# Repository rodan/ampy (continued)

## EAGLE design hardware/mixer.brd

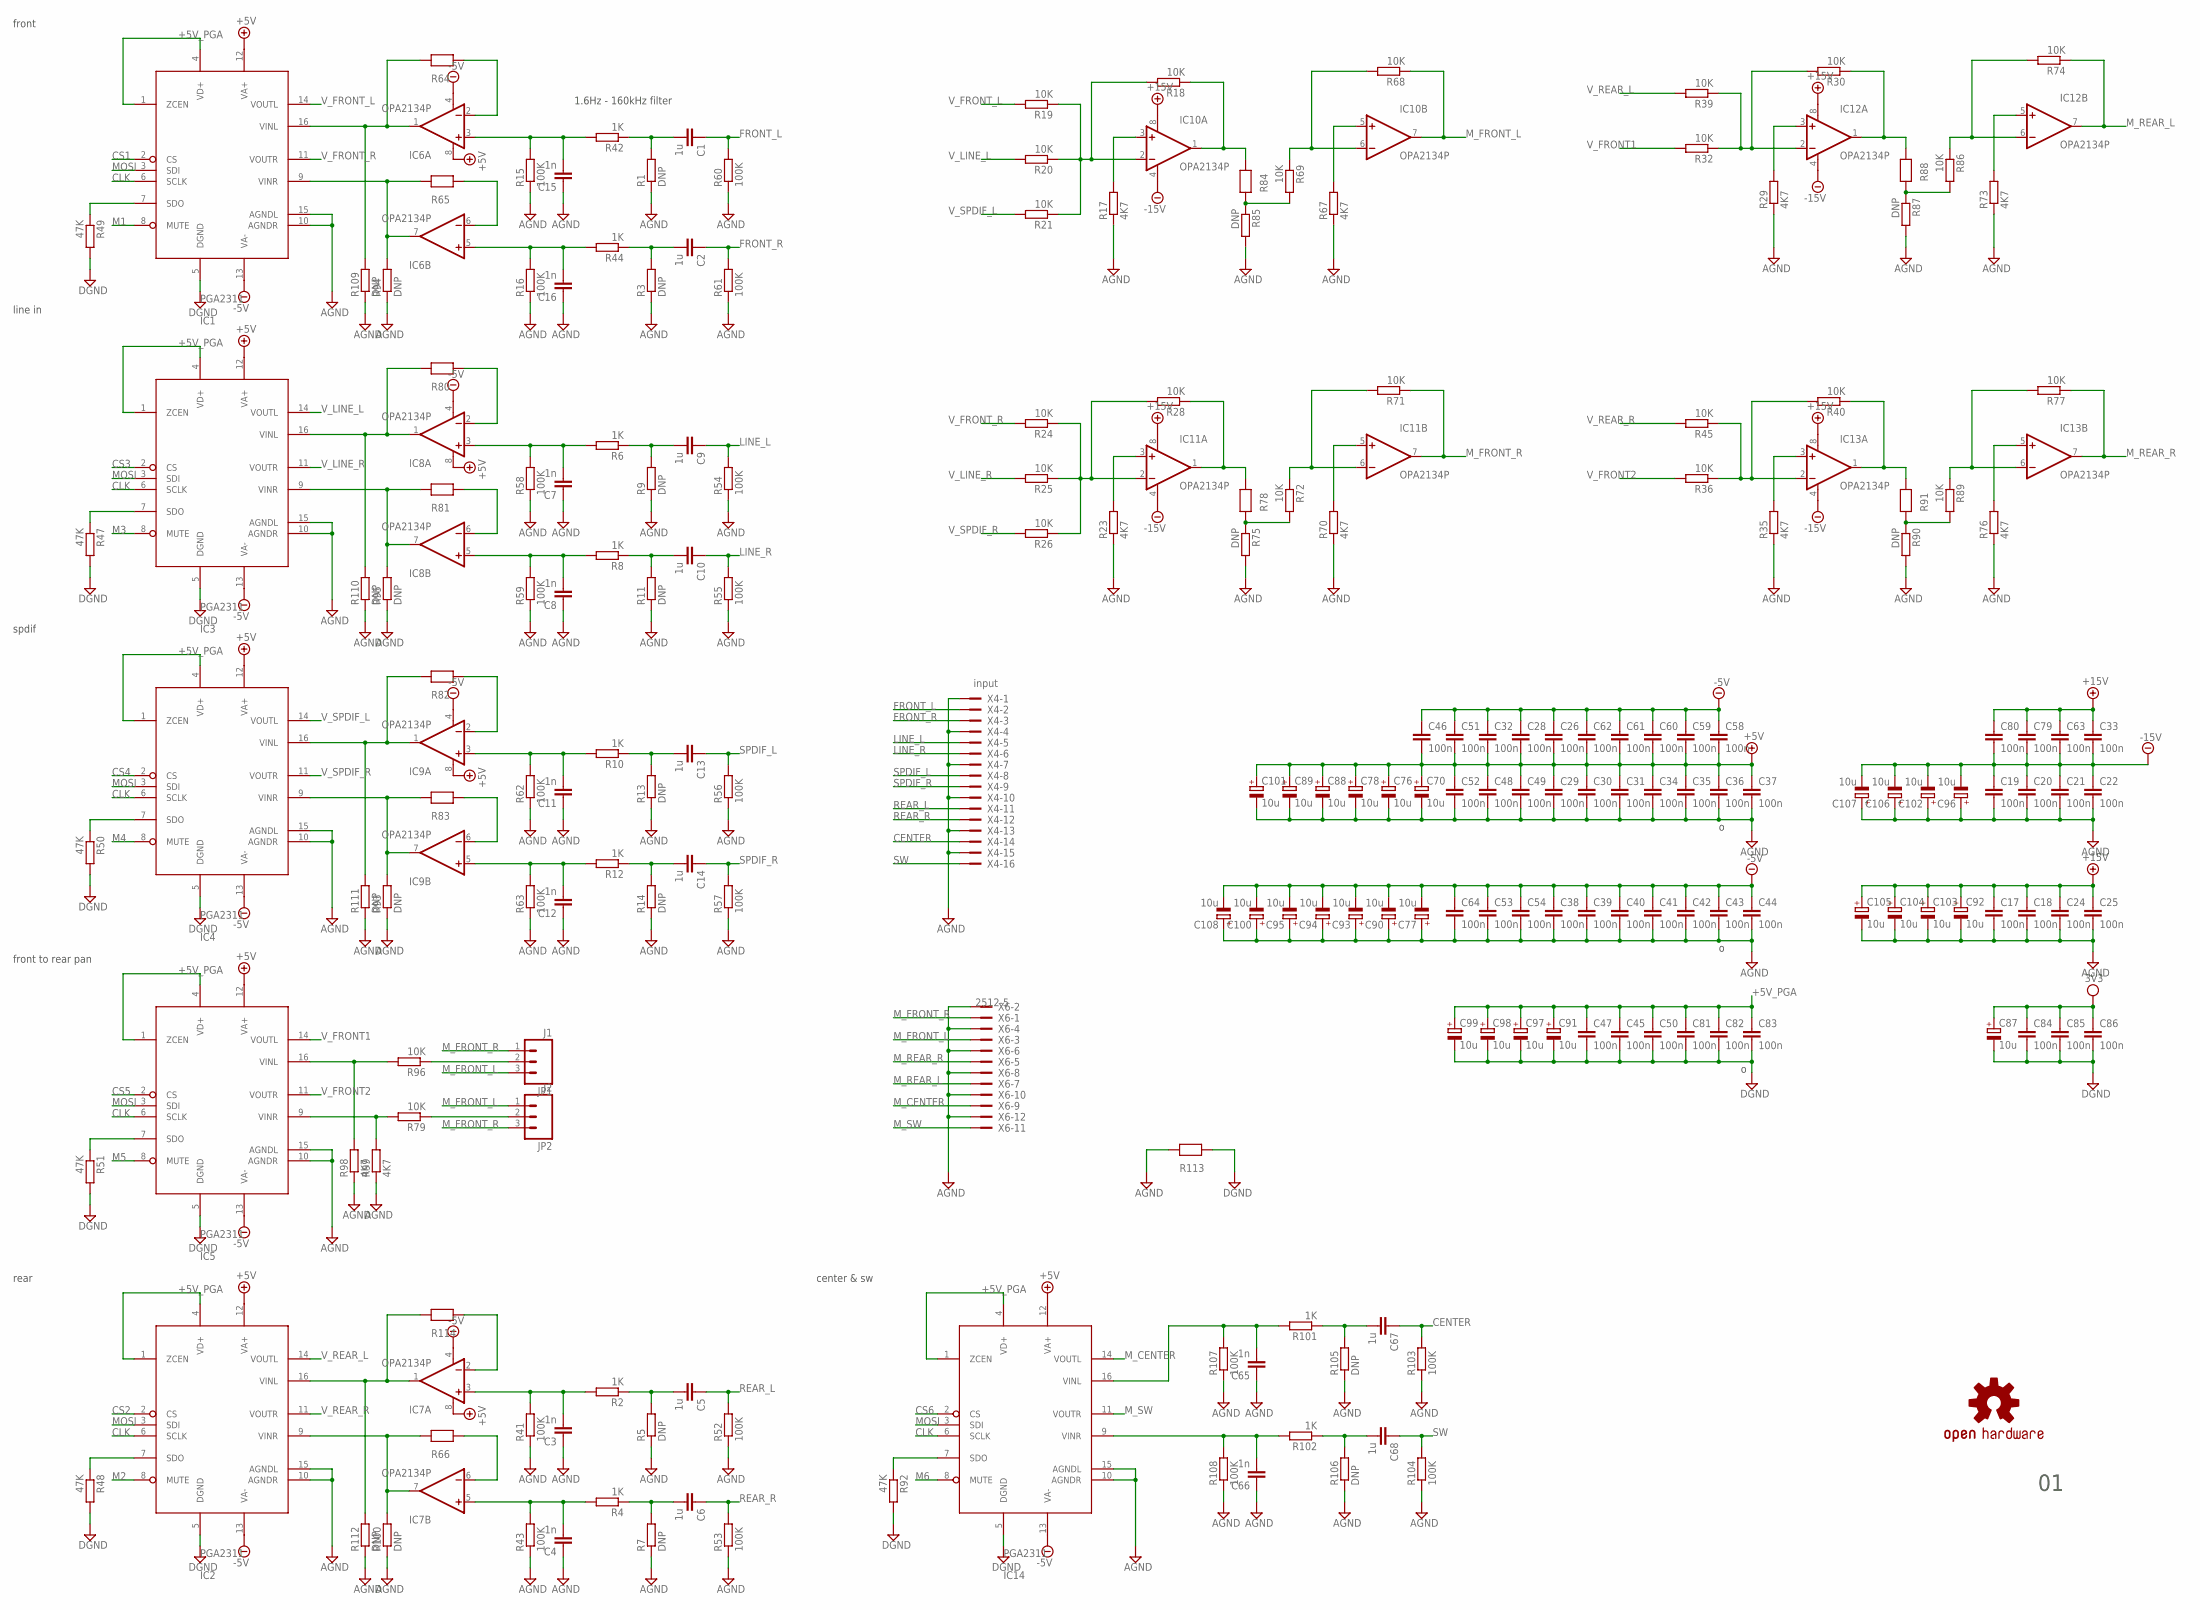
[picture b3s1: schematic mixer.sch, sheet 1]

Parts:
C1, C2, C5, C6, C9, C10, C13, C14, C67, C68: 1u; C0805
C3, C4, C7, C8, C11, C12, C15, C16, C65, C66: 1n; C0805
C17, C18, C19, C20, C21, C22, C24, C25, C26, C28, C29, C30, C31, C32, C33, C34, C35, C36, C37, C38, C39, C40, C41, C42, C43, C44, C45, C46, C47, C48, C49, C50, C51, C52, C53, C54, C58, C59, C60, C61, C62, C63, C64, C79, C80, C81, C82, C83, C84, C85, C86: 100n; C0805
C70, C76, C77, C78, C87, C88, C89, C90, C91, C92, C93, C94, C95, C96, C97, C98, C99, C100, C101, C102, C103, C104, C105, C106, C107, C108: 10u; 153CLV-0405
IC1, IC2, IC3, IC4, IC5, IC14: PGA2311; SO-16
IC6, IC7, IC8, IC9, IC10, IC11, IC12, IC13: OPA2134P; DIL08
JP1: J1; 1X03
JP2: J2; 1X03
R1, R3, R5, R7, R9, R11, R13, R14, R75, R85, R87, R90, R93, R94, R95, R100, R105, R106, R109, R110, R111, R112: DNP; R0805W
R2, R4, R6, R8, R10, R12, R42, R44, R101, R102: 1K; R0805W
R15, R16, R41, R43, R52, R53, R54, R55, R56, R57, R58, R59, R60, R61, R62, R63, R103, R104, R107, R108: 100K; R0805W
R17, R23, R29, R35, R67, R70, R73, R76, R98, R99: 4K7; R0805W
R18, R19, R20, R21, R24, R25, R26, R28, R30, R32, R36, R39, R40, R45, R68, R69, R71, R72, R74, R77, R79, R86, R89, R96: 10K; R0805W
R47, R48, R49, R50, R51, R92: 47K; R0805W
R64, R65, R66, R78, R80, R81, R82, R83, R84, R88, R91, R113, R114: 0R_0805; R0805W
U$7: OSHW-LOGOM; OSHW-LOGO-M
X4: input; PAK100/2500-5-16
X6: 2512-5; PAK100/2500-5-12

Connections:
3V3: C84.1, C85.1, C86.1, C87.+; also elsewhere on the board
+5V: C26.2, C28.2, C29.1, C30.1, C31.1, C32.2, C34.1, C35.1, C36.1, C37.1, C46.2, C48.1, C49.1, C51.2, C52.1, C58.2, C59.2, C60.2, C61.2, C62.2, C70.+, C76.+, C78.+, C88.+, C89.+, C101.+, IC1.12 (VA+), IC2.12 (VA+), IC3.12 (VA+), IC4.12 (VA+), IC5.12 (VA+), IC6.8 (V+), IC7.8 (V+), IC8.8 (V+), IC9.8 (V+), IC14.12 (VA+); also elsewhere on the board
+5V_PGA: C45.1, C47.1, C50.1, C81.1, C82.1, C83.1, C91.+, C97.+, C98.+, C99.+, IC1.1 (ZCEN), IC1.4 (VD+), IC2.1 (ZCEN), IC2.4 (VD+), IC3.1 (ZCEN), IC3.4 (VD+), IC4.1 (ZCEN), IC4.4 (VD+), IC5.1 (ZCEN), IC5.4 (VD+), IC14.1 (ZCEN), IC14.4 (VD+); also elsewhere on the board
+15V: C17.1, C18.1, C24.1, C25.1, C33.1, C63.1, C79.1, C80.1, C92.+, C103.+, C104.+, C105.+, IC10.8 (V+), IC11.8 (V+), IC12.8 (V+), IC13.8 (V+); also elsewhere on the board
-5V: C26.1, C28.1, C32.1, C38.1, C39.1, C40.1, C41.1, C42.1, C43.1, C44.1, C46.1, C51.1, C53.1, C54.1, C58.1, C59.1, C60.1, C61.1, C62.1, C64.1, C77.-, C90.-, C93.-, C94.-, C95.-, C100.-, C108.-, IC1.13 (VA-), IC2.13 (VA-), IC3.13 (VA-), IC4.13 (VA-), IC5.13 (VA-), IC6.4 (V-), IC7.4 (V-), IC8.4 (V-), IC9.4 (V-), IC14.13 (VA-); also elsewhere on the board
-15V: C19.1, C20.1, C21.1, C22.1, C33.2, C63.2, C79.2, C80.2, C96.-, C102.-, C106.-, C107.-, IC10.4 (V-), IC11.4 (V-), IC12.4 (V-), IC13.4 (V-); also elsewhere on the board
AGND: C3.1, C4.1, C7.1, C8.1, C11.1, C12.1, C15.1, C16.1, C17.2, C18.2, C19.2, C20.2, C21.2, C22.2, C24.2, C25.2, C29.2, C30.2, C31.2, C34.2, C35.2, C36.2, C37.2, C38.2, C39.2, C40.2, C41.2, C42.2, C43.2, C44.2, C48.2, C49.2, C52.2, C53.2, C54.2, C64.2, C65.1, C66.1, C70.-, C76.-, C77.+, C78.-, C88.-, C89.-, C90.+, C92.-, C93.+, C94.+, C95.+, C96.+, C100.+, C101.-, C102.+, C103.-, C104.-, C105.-, C106.+, C107.+, C108.+, IC1.10 (AGNDR), IC1.15 (AGNDL), IC2.10 (AGNDR), IC2.15 (AGNDL), IC3.10 (AGNDR), IC3.15 (AGNDL), IC4.10 (AGNDR), IC4.15 (AGNDL), IC5.10 (AGNDR), IC5.15 (AGNDL), IC14.10 (AGNDR), IC14.15 (AGNDL), R1.1, R3.1, R5.1, R7.1, R9.1, R11.1, R13.1, R14.1, R15.1, R16.1, R17.1, R23.1, R29.1, R35.1, R41.1, R43.1, R52.1, R53.1, R54.1, R55.1, R56.1, R57.1, R58.1, R59.1, R60.1, R61.1, R62.1, R63.1, R67.1, R70.1, R73.1, R75.2, R76.1, R85.2, R87.2, R90.2, R93.1, R94.1, R95.1, R98.1, R99.1, R100.1, R103.1, R104.1, R105.1, R106.1, R107.1, R108.1, R109.1, R110.1, R111.1, R112.1, R113.1, X4.1, X4.4, X4.7, X4.10, X4.13, X4.15, X6.2, X6.4, X6.6, X6.8, X6.10, X6.12; also elsewhere on the board
CENTER: C67.1, R103.2, X4.14
CLK: IC1.6 (SCLK), IC2.6 (SCLK), IC3.6 (SCLK), IC4.6 (SCLK), IC5.6 (SCLK), IC14.6 (SCLK); also elsewhere on the board
CS1: IC1.2 (CS); also elsewhere on the board
CS2: IC2.2 (CS); also elsewhere on the board
CS3: IC3.2 (CS); also elsewhere on the board
CS4: IC4.2 (CS); also elsewhere on the board
CS5: IC5.2 (CS); also elsewhere on the board
CS6: IC14.2 (CS); also elsewhere on the board
DGND: C45.2, C47.2, C50.2, C81.2, C82.2, C83.2, C84.2, C85.2, C86.2, C87.-, C91.-, C97.-, C98.-, C99.-, IC1.5 (DGND), IC2.5 (DGND), IC3.5 (DGND), IC4.5 (DGND), IC5.5 (DGND), IC14.5 (DGND), R47.2, R48.2, R49.2, R50.2, R51.2, R92.2, R113.2; also elsewhere on the board
FRONT_L: C1.1, R60.2, X4.2
FRONT_R: C2.1, R61.2, X4.3
LINE_L: C9.1, R54.2, X4.5
LINE_R: C10.1, R55.2, X4.6
M1: IC1.8 (MUTE); also elsewhere on the board
M2: IC2.8 (MUTE); also elsewhere on the board
M3: IC3.8 (MUTE); also elsewhere on the board
M4: IC4.8 (MUTE); also elsewhere on the board
M5: IC5.8 (MUTE); also elsewhere on the board
M6: IC14.8 (MUTE); also elsewhere on the board
MOSI: IC1.3 (SDI), IC2.3 (SDI), IC3.3 (SDI), IC4.3 (SDI), IC5.3 (SDI), IC14.3 (SDI); also elsewhere on the board
M_CENTER: IC14.14 (VOUTL), X6.9
M_FRONT_L: IC10.7 (OUT), JP1.3, JP2.1, R68.1, X6.3
M_FRONT_R: IC11.7 (OUT), JP1.1, JP2.3, R71.1, X6.1
M_REAR_L: IC12.7 (OUT), R74.1, X6.7
M_REAR_R: IC13.7 (OUT), R77.1, X6.5
M_SW: IC14.11 (VOUTR), X6.11
unnamed: C1.2, R1.2, R42.1
unnamed: C2.2, R3.2, R44.1
unnamed: IC14.7 (SDO), R92.1
unnamed: IC2.16 (VINL), IC7.1 (OUT), R112.2, R114.1
unnamed: IC1.16 (VINL), IC6.1 (OUT), R64.1, R109.2
unnamed: IC2.9 (VINR), IC7.7 (OUT), R66.1, R100.2
unnamed: C4.2, IC7.5 (+IN), R4.2, R43.2
unnamed: C3.2, IC7.3 (+IN), R2.2, R41.2
unnamed: C5.2, R2.1, R5.2
unnamed: C6.2, R4.1, R7.2
unnamed: IC3.16 (VINL), IC8.1 (OUT), R80.1, R110.2
unnamed: IC3.9 (VINR), IC8.7 (OUT), R81.1, R95.2
unnamed: IC1.9 (VINR), IC6.7 (OUT), R65.1, R94.2
unnamed: C8.2, IC8.5 (+IN), R8.2, R59.2
unnamed: IC4.16 (VINL), IC9.1 (OUT), R82.1, R111.2
unnamed: C7.2, IC8.3 (+IN), R6.2, R58.2
unnamed: C9.2, R6.1, R9.2
unnamed: C10.2, R8.1, R11.2
unnamed: C65.2, IC14.16 (VINL), R101.2, R107.2
unnamed: IC4.9 (VINR), IC9.7 (OUT), R83.1, R93.2
unnamed: C12.2, IC9.5 (+IN), R12.2, R63.2
unnamed: C11.2, IC9.3 (+IN), R10.2, R62.2
unnamed: C16.2, IC6.5 (+IN), R16.2, R44.2
unnamed: C13.2, R10.1, R13.2
unnamed: C14.2, R12.1, R14.2
unnamed: C15.2, IC6.3 (+IN), R15.2, R42.2
unnamed: C66.2, IC14.9 (VINR), R102.2, R108.2
unnamed: JP1.2, R96.1
unnamed: IC6.2 (-IN), R64.2
unnamed: IC5.16 (VINL), R96.2, R98.2
unnamed: IC6.6 (-IN), R65.2
unnamed: IC1.7 (SDO), R49.1
unnamed: IC3.7 (SDO), R47.1
unnamed: IC10.3 (+IN), R17.2
unnamed: IC10.2 (-IN), R18.2, R19.1, R20.1, R21.1
unnamed: IC7.2 (-IN), R114.2
unnamed: IC10.1 (OUT), R18.1, R84.2
unnamed: IC7.6 (-IN), R66.2
unnamed: IC13.2 (-IN), R36.1, R40.2, R45.1
unnamed: IC11.3 (+IN), R23.2
unnamed: IC11.2 (-IN), R24.1, R25.1, R26.1, R28.2
unnamed: IC10.5 (+IN), R67.2
unnamed: IC10.6 (-IN), R68.2, R69.1
unnamed: IC8.2 (-IN), R80.2
unnamed: IC2.7 (SDO), R48.1
unnamed: IC12.3 (+IN), R29.2
unnamed: IC4.7 (SDO), R50.1
unnamed: IC11.5 (+IN), R70.2
unnamed: C67.2, R101.1, R105.2
unnamed: C68.2, R102.1, R106.2
unnamed: IC13.3 (+IN), R35.2
unnamed: IC5.7 (SDO), R51.1
unnamed: IC11.6 (-IN), R71.2, R72.1
unnamed: IC8.6 (-IN), R81.2
unnamed: IC12.5 (+IN), R73.2
unnamed: IC12.6 (-IN), R74.2, R86.1
unnamed: IC9.2 (-IN), R82.2
unnamed: IC13.5 (+IN), R76.2
unnamed: IC13.6 (-IN), R77.2, R89.1
unnamed: IC9.6 (-IN), R83.2
unnamed: IC12.2 (-IN), R30.2, R32.1, R39.1
unnamed: IC11.1 (OUT), R28.1, R78.2
unnamed: IC12.1 (OUT), R30.1, R88.2
unnamed: R69.2, R84.1, R85.1
unnamed: IC13.1 (OUT), R40.1, R91.2
unnamed: IC5.9 (VINR), R79.2, R99.2
unnamed: JP2.2, R79.1
unnamed: R72.2, R75.1, R78.1
unnamed: R86.2, R87.1, R88.1
unnamed: R89.2, R90.1, R91.1
REAR_L: C5.1, R52.2, X4.11
REAR_R: C6.1, R53.2, X4.12
SPDIF_L: C13.1, R56.2, X4.8
SPDIF_R: C14.1, R57.2, X4.9
SW: C68.1, R104.2, X4.16
V_FRONT1: IC5.14 (VOUTL), R32.2
V_FRONT2: IC5.11 (VOUTR), R36.2
V_FRONT_L: IC1.14 (VOUTL), R19.2
V_FRONT_R: IC1.11 (VOUTR), R24.2
V_LINE_L: IC3.14 (VOUTL), R20.2
V_LINE_R: IC3.11 (VOUTR), R25.2
V_REAR_L: IC2.14 (VOUTL), R39.2
V_REAR_R: IC2.11 (VOUTR), R45.2
V_SPDIF_L: IC4.14 (VOUTL), R21.2
V_SPDIF_R: IC4.11 (VOUTR), R26.2

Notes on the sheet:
rear
line in
spdif
front to rear pan
front
1.6Hz - 160kHz filter
center & sw

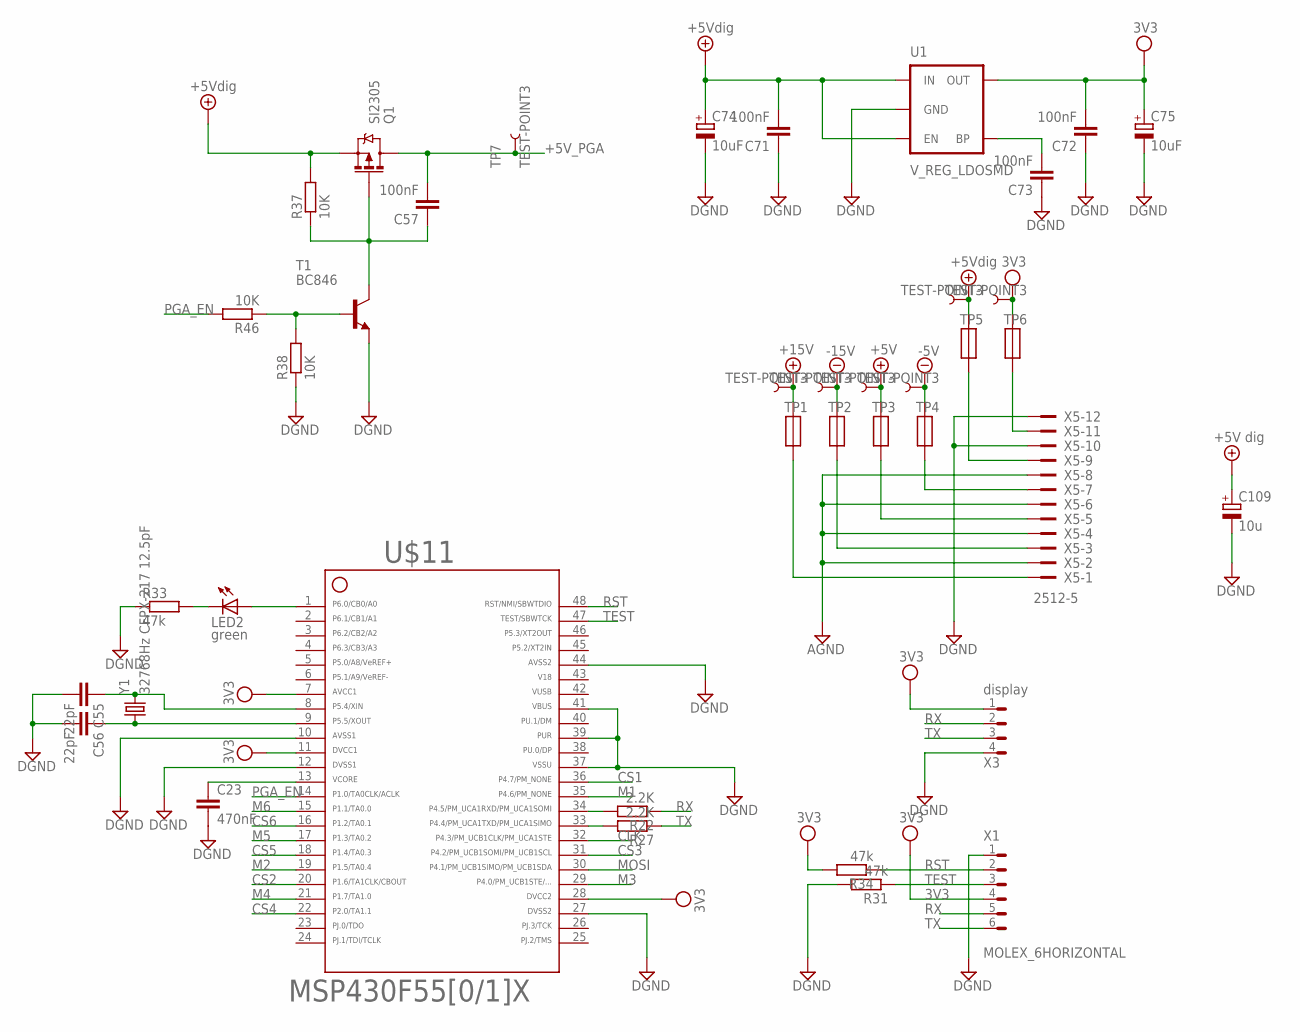
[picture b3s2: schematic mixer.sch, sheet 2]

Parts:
C23: 470nF; C0805
C55, C56: 22pF; C0805
C57, C71, C72, C73: 100nF; C0805
C74, C75: 10uF; 153CLV-0405
C109: 10u; 153CLV-0405
LED2: green; CHIPLED_0805
Q1: SI2305; SOT23-3_POWER
R22, R27: 2.2K; R0805W
R31, R33, R34: 47k; R0805W
R37, R38, R46: 10K; R0805W
T1: BC846; SOT23
TP1, TP2, TP3, TP4, TP5, TP6, TP7: TEST-POINT3; PAD.03X.03
U1: V_REG_LDOSMD; SOT23-5
U$2, U$5, U$6, U$9, U$12, U$13: RESETTABLE; 1210
U$11: F55[0/1]X---PT48; PT48
X1: MOLEX_6HORIZONTAL; 0530480610
X3: display; 0530480401
X5: 2512-5; PAK100/2500-5-12
Y1: 32768Hz CFPX-217 12.5pF; CRYSTAL-SMD-3.2X1.5

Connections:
3V3: C72.2, C75.+, R34.2, TP6.P$1, U1.5 (OUT), U$11.7, U$11.11, U$11.28, U$13.P$2, X1.4, X3.1; also elsewhere on the board
42: U$11.42
43: U$11.43
46: U$11.46
+5V: TP3.P$1, U$6.P$2; also elsewhere on the board
+5V/1: C71.2, C74.+, C109.+, Q1.2 (S), R37.2, TP5.P$1, U1.1 (IN), U1.3 (EN), U$12.P$2
+5V_PGA: C57.2, Q1.3 (D), TP7.P$1; also elsewhere on the board
+15V: TP1.P$1, U$2.P$2; also elsewhere on the board
-5V: TP4.P$1, U$9.P$2; also elsewhere on the board
-15V: TP2.P$1, U$5.P$2; also elsewhere on the board
AGND: X5.2, X5.4, X5.6, X5.8; also elsewhere on the board
CLK: U$11.32; also elsewhere on the board
CS1: U$11.36; also elsewhere on the board
CS2: U$11.20; also elsewhere on the board
CS3: U$11.31; also elsewhere on the board
CS4: U$11.22; also elsewhere on the board
CS5: U$11.18; also elsewhere on the board
CS6: U$11.16; also elsewhere on the board
DGND: C23.2, C55.2, C56.2, C71.1, C72.1, C73.1, C74.-, C75.-, C109.-, R31.2, R33.1, R38.1, T1.2 (E), U1.2 (GND), U$11.10, U$11.12, U$11.27, U$11.37, U$11.39, U$11.41, U$11.44, X1.1, X3.4, X5.10, X5.12; also elsewhere on the board
M1: U$11.35; also elsewhere on the board
M2: U$11.19; also elsewhere on the board
M3: U$11.29; also elsewhere on the board
M4: U$11.21; also elsewhere on the board
M5: U$11.17; also elsewhere on the board
M6: U$11.15; also elsewhere on the board
MOSI: U$11.30; also elsewhere on the board
unnamed: LED2.A, U$11.1
unnamed: C23.1, U$11.13
unnamed: C56.1, U$11.9, Y1.P$1 (1)
unnamed: C55.1, U$11.8, Y1.P$2 (2)
unnamed: LED2.C, R33.2
unnamed: C57.1, Q1.1 (G), R37.1, T1.3 (C)
unnamed: R38.2, R46.1, T1.1 (B)
unnamed: C73.2, U1.4 (BP)
unnamed: U$2.P$1, X5.1
unnamed: U$5.P$1, X5.3
unnamed: U$6.P$1, X5.5
unnamed: U$9.P$1, X5.7
unnamed: U$12.P$1, X5.9
unnamed: U$13.P$1, X5.11
P4.4: R27.2, U$11.33
P4.5: R22.2, U$11.34
PGA_EN: R46.2, U$11.14
RST: R34.1, U$11.48, X1.2
RX/SDA: R22.1, X1.5, X3.2; also elsewhere on the board
TEST: R31.1, U$11.47, X1.3
TX/SCL: R27.1, X1.6, X3.3; also elsewhere on the board

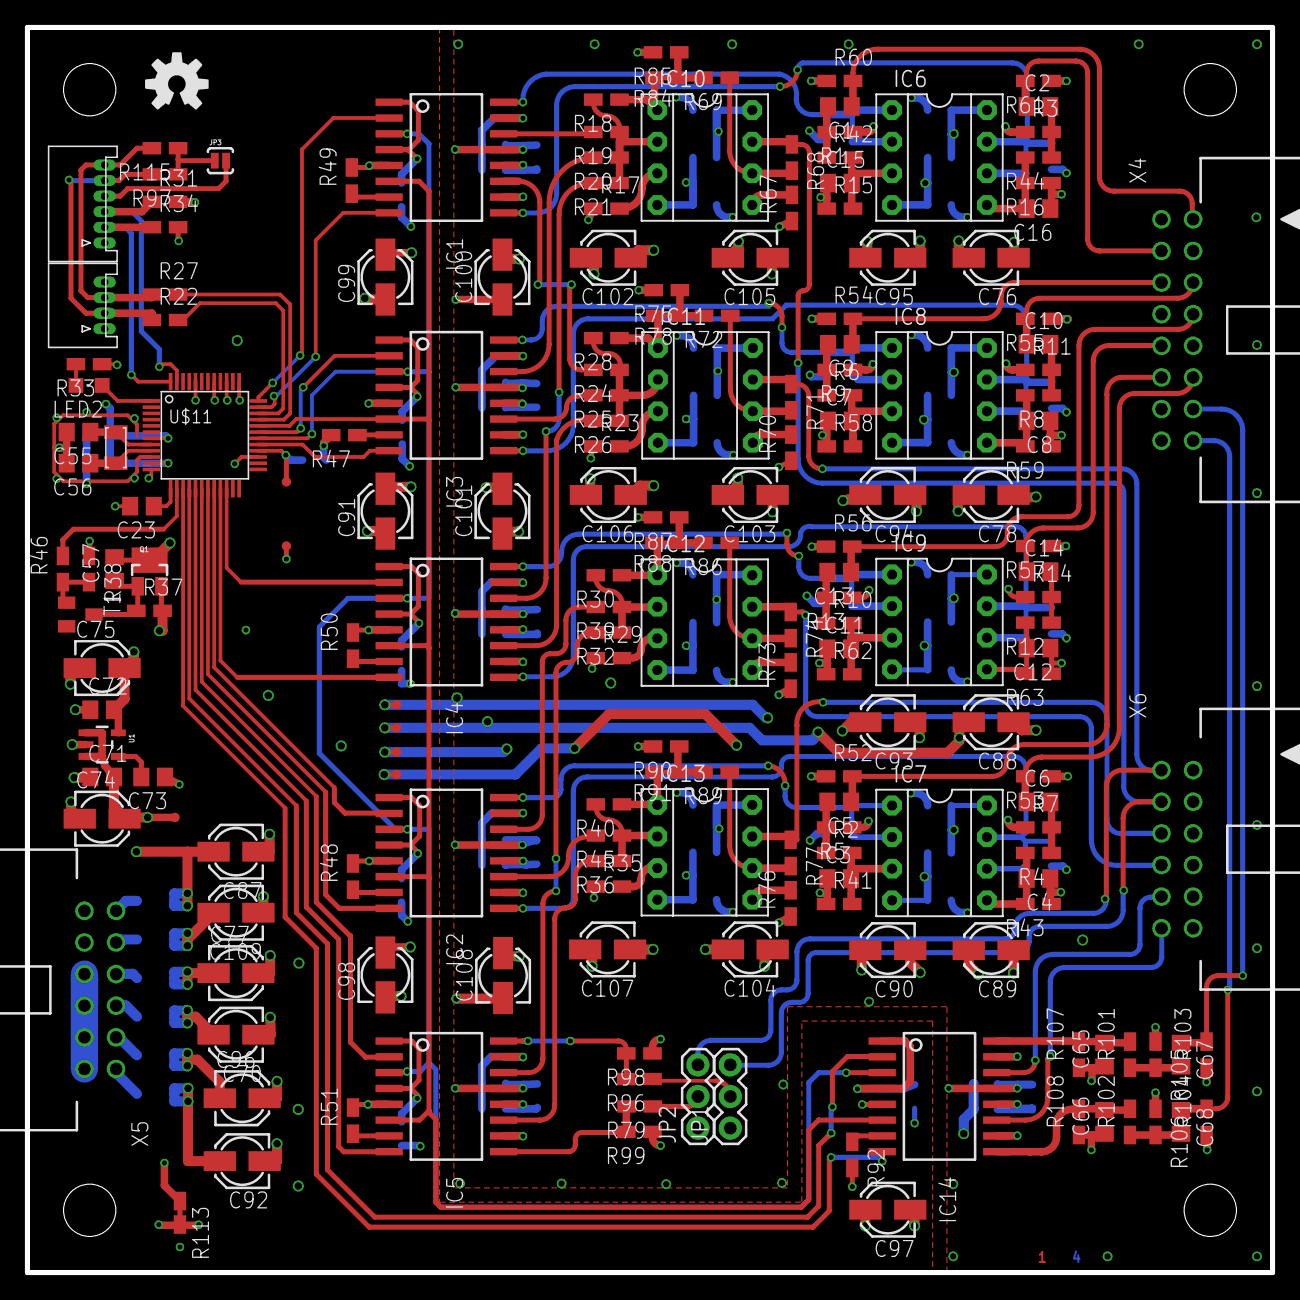
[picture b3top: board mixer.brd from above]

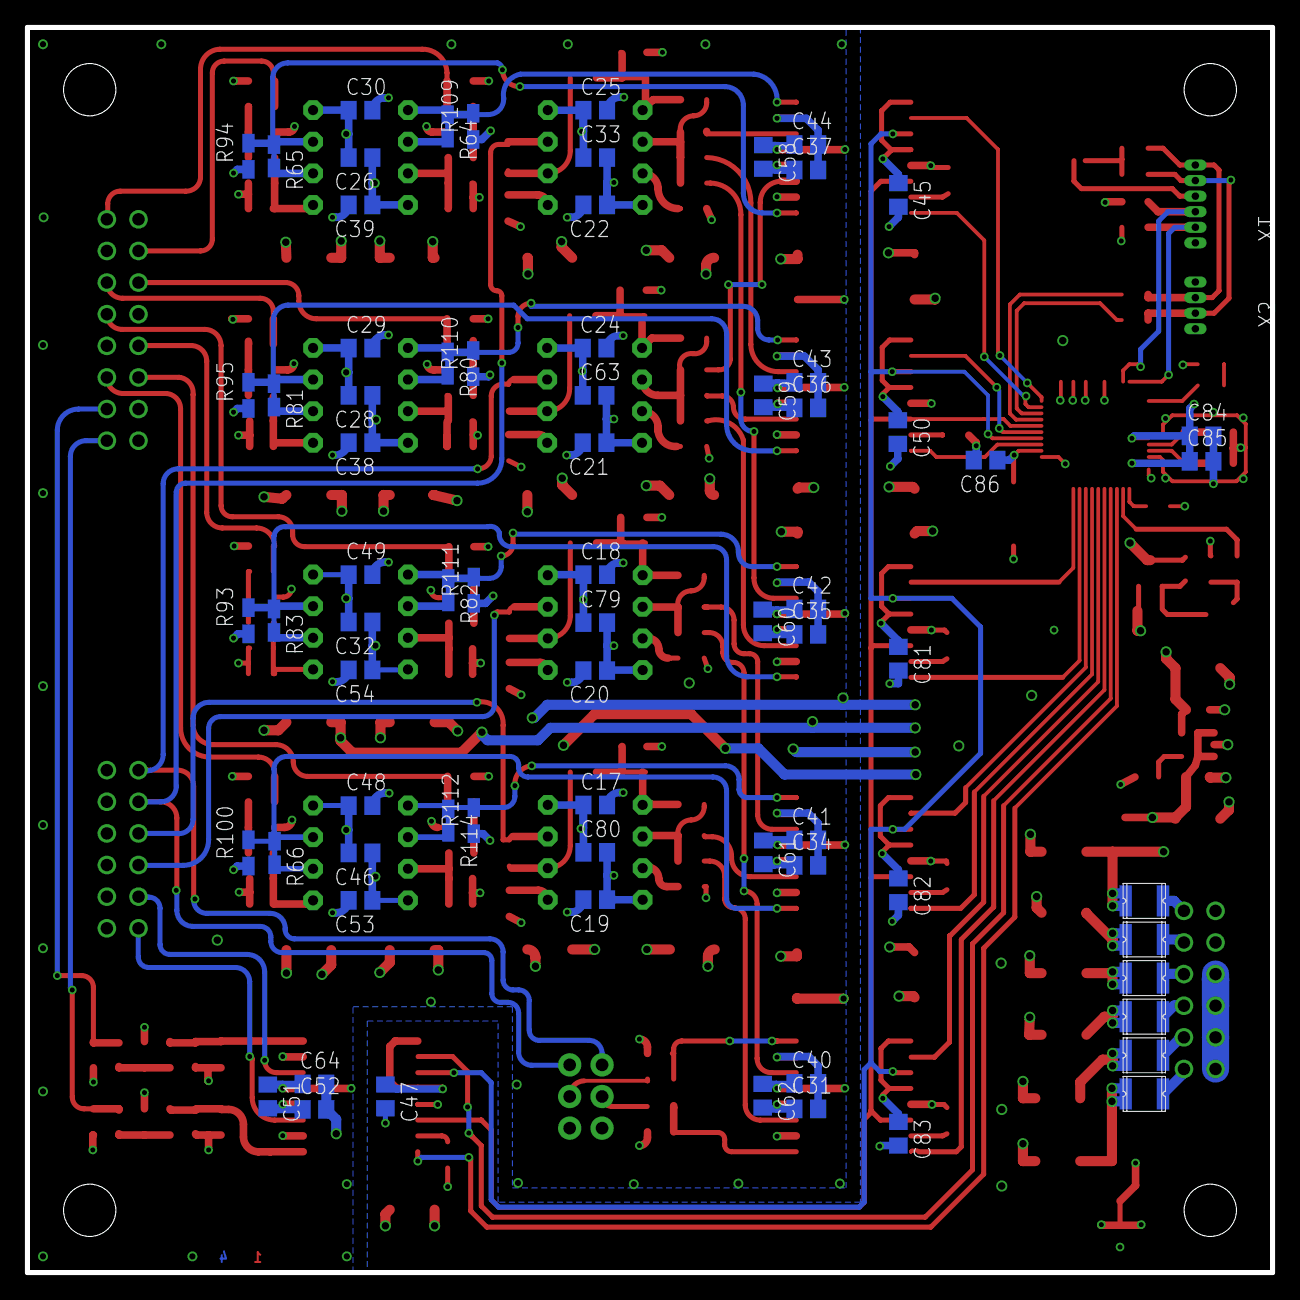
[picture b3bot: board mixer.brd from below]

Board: 4 copper layers, 100.0 x 100.0 mm, 264 parts (73 on the bottom side), 141 nets.

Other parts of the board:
JP3: SJ_2S-NO
R97, R115: NA/4K7; R0805W

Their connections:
3V3: JP3.2; also elsewhere on the board
unnamed: JP3.1, R97.1, R115.1
RX/SDA: R97.2; also elsewhere on the board
TX/SCL: R115.2; also elsewhere on the board

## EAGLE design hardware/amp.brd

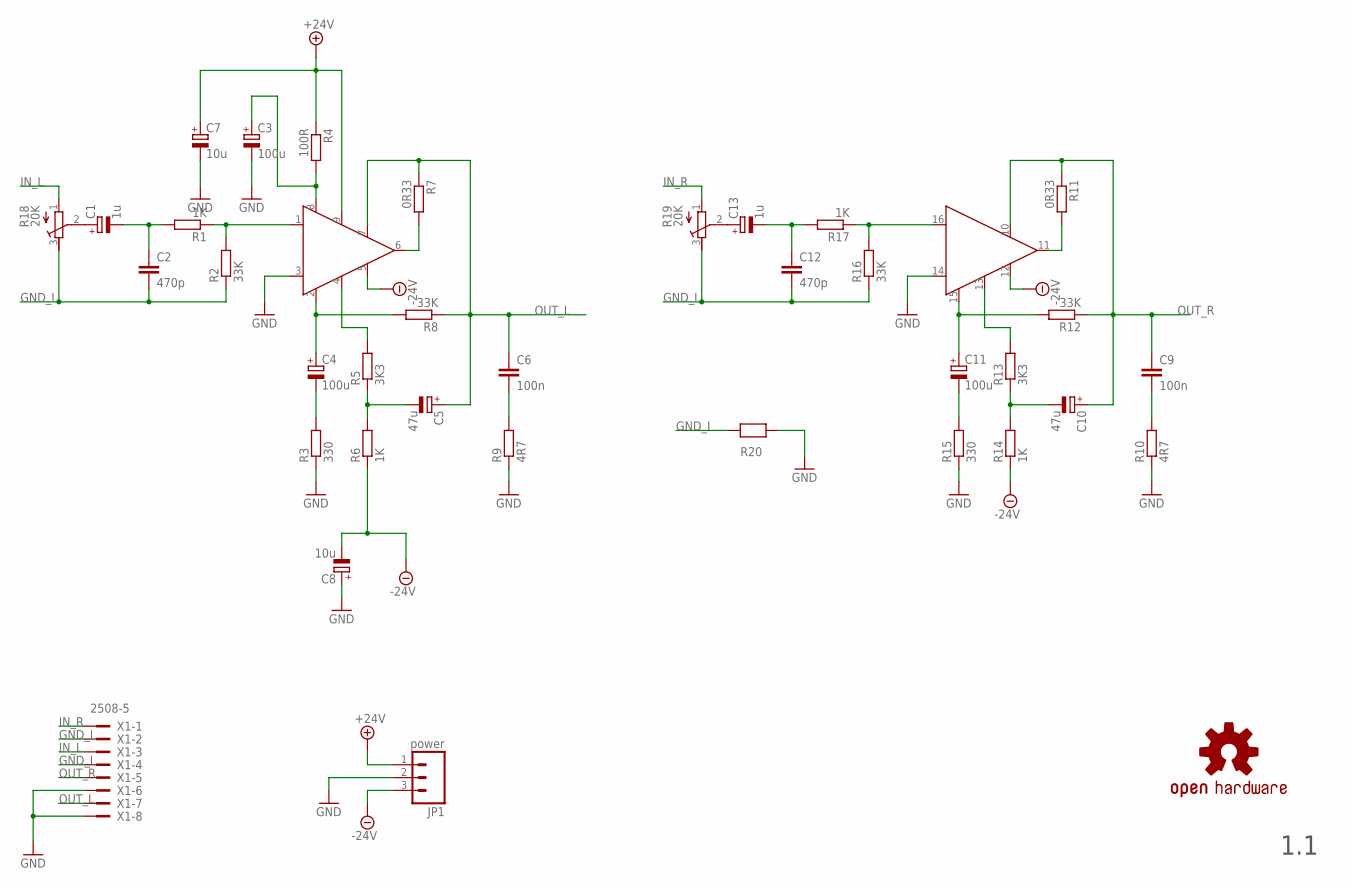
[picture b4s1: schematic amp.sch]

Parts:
C1, C13: 1u; PANASONIC_B
C2, C12: 470p; C0805
C3, C4, C11: 100u; PANASONIC_G
C5, C10: 47u; PANASONIC_F
C6, C9: 100n; C10B5
C7, C8: 10u; PANASONIC_D
JP1: power; 1X03
R1, R17: 1K; R0805W
R2, R16: 33K; R0805W
R3, R15: 330; P0613/15
R4: 100R; P0613/15
R5, R13: 3K3; P0613/15
R6, R14: 1K; P0613/15
R7, R11: 0R33; P0613/15
R8, R12: 33K; P0613/15
R9, R10: 4R7; P0613/15
R18, R19: 20K; RTRIM3339P
R20: 0R_0805; R0805W
U$1: STK465HORIZ-BOTTOM; STK465-HB
U$7: OSHW-LOGOM; OSHW-LOGO-M
X1: 2508-5; PAK100/2500-5-08

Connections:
+24V: C7.+, JP1.1, R4.1, U$1.9
-24V: C8.-, JP1.3, R6.1, R14.1, U$1.5, U$1.12
GND: C3.-, C7.-, C8.+, JP1.2, R3.1, R9.1, R10.1, R15.1, R20.2, U$1.3, U$1.14, X1.6, X1.8
GND_I: C2.2, C12.2, R2.1, R16.1, R18.3 (E), R19.3 (E), R20.1, X1.2, X1.4
IN_L: R18.1 (A), X1.3
IN_R: R19.1 (A), X1.1
unnamed: C4.-, R3.2
unnamed: C4.+, R8.2, U$1.2
unnamed: C5.-, R5.1, R6.2
unnamed: C6.2, R9.2
unnamed: R7.2, U$1.6
unnamed: C3.+, R4.2, U$1.8
unnamed: R5.2, U$1.4
unnamed: R1.1, R2.2, U$1.1
unnamed: C1.-, C2.1, R1.2
unnamed: C1.+, R18.2 (S)
unnamed: C13.+, R19.2 (S)
unnamed: R11.2, U$1.11
unnamed: C11.-, R15.2
unnamed: R16.2, R17.1, U$1.16
unnamed: C12.1, C13.-, R17.2
unnamed: C11.+, R12.2, U$1.15
unnamed: C10.-, R13.1, R14.2
unnamed: R13.2, U$1.13
unnamed: C9.2, R10.2
OUT_L: C5.+, C6.1, R7.1, R8.1, U$1.7, X1.7
OUT_R: C9.1, C10.+, R11.1, R12.1, U$1.10, X1.5

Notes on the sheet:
1.1

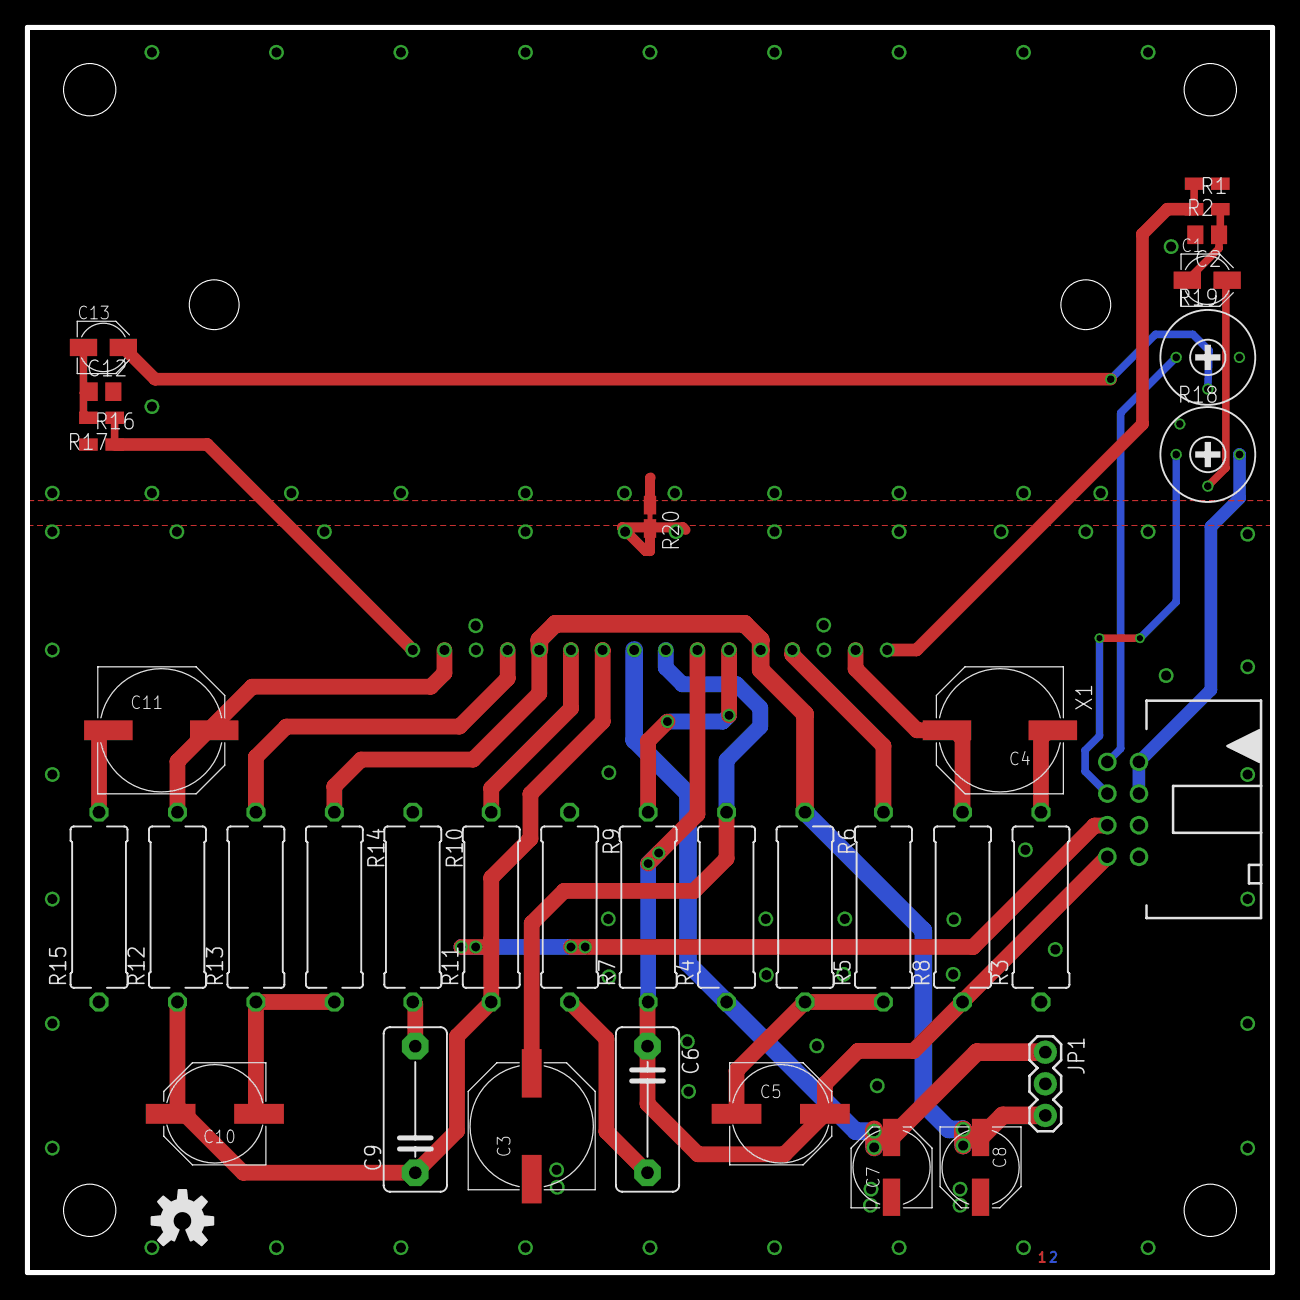
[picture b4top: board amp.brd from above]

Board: 4 copper layers, 100.0 x 100.0 mm, 37 parts (0 on the bottom side), 27 nets.
